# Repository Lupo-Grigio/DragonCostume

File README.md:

# DragonCostume 
Repository for all code and designs used in my massive dragon head and costume

/Dragon Head 

  -/Lights 
    Internal LED strips
    Running WLED on an esp32 to power the primary LED Light Strips within the head (Fork minimal changes) (Dev environment is Platform.io in VSCode)
    The strip "Map" or definitions are created from a google sheets spreadsheet, The regions are created using several pivot tables

    -/WLED
      clone of WLED source from https://github.com/Aircoookie/WLED I _think_ this directory should be a fork.. but maybe if I actually make changes. this tweak is to get WLED to work on one of @romkey's discoball ESP32-dev boards. 

    -/WoWki Simulations
      Several test FASTLED simulations of the head strips coded up in WoKwi - no production code
      makes a convient(Where is my spell checker?) way to simulate the LED strips.

  -/Eyes Controllable Animated Eyes
    Animated Eyes powered by an Adafruit Monster M4sk with custom code (fork) (Dev environment is both Arduino and Platform.io)
    Animated eye gaze direction is controlled by face detection done on an ESP32-WROVER-DEV Test framework is based on the ESP32-cam "camera" demo(Dev environment is both Arduino and Platform.io, but issue with Platform.io causes mem management failure in face detection)
    Some example code created for sscanf and parameter passing coded in wowki
    Physical Joystic control of the eyes powered by an ADAFRUIT Joy Feather and Feather wing : In Progress

      -/M4_Eyes Based off of TonyLHansen's merge request into Adafruit's main. His code includes some extra eye controls and code for user.cpp files getting config info from the config file. Will be handy for me to set the BAUD rate between controller and the mask. https://github.com/adafruit/Adafruit_Learning_System_Guides/pull/915/commits/2b4827c8276a8fa8b2f16dbccf2c00a39fa4a631
    
      -/ESP32-Eye-Tracker
        Based on the ESP32-Camera-Eye-tracker-DEMO, Wifi removed, with web server assocated code removed. This Just captures video and does face detection, if it finds a face it writes it out to serial2
        Face detection running in the DEMO gets about 2.3 frames a second
        Face detection running in the Eye Tracker about 2.7 This ended up being a bit of a waste of time. I strongly suspect the face recognition is baced on OpenCV's v3 HAAR cascade face detection rather than the better, smaller, more efficient DNN face detection which appeared in opencv 4 (or 4.1 can't remember to lazy to look up). 

      -/ESP32-Camera-Eye-tracker-DEMO
      Cloned from the ESP32-CAM/example and fixed via this commentary https://github.com/espressif/arduino-esp32/issues/5128. This directory contains the mirror code for M4_Eyes, this is the "controller" part. This does facial detection, and sends tracking data out serial port. This code is written for the Freenove ESP32-WROVER-DEV module with camera. https://www.amazon.com/Freenove-ESP32-WROVER-Bluetooth-Compatible-Tutorials/dp/B09BC5CNHM?ref_=ast_sto_dp This demo code runs a webserver and streams video, and contains VERBOSE debugging info written to the USB serial port. Face location data is written to serial 2 which is configured on pins 2 and 15, the format of the message and which pin is TX and RX are in the code. 

      -/Prototype Case
      3d printable case for the face tracking eye demo. Designed to hold the ESP32-CAM module and the Adafruit Monster M4sk. Originally designed in tinkercad by importing the case designed by adafruit for the M4sk. Tinkercad link:https://www.tinkercad.com/things/l33OCsHAKPb-eye-camera-mask-case also can be found on thingaverse: https://www.thingiverse.com/thing:5188566

      -/M4SK PWM remapping example
      Sample code for the Adafruit M4SK that just remaps the PWM port as Serial2 reads from it and writes to the USB serial monitor

      -/ESP32-CAM second serial sample
      A tiny project containing an example of setting up an ESP32-CAM to write data to pins 15 and 2, also a bit of beginner examples of passing pointers and structs. Developed and simulated on Wokwi. See the Wokwi-project.txt for link

  -Forward Cameras and Performer HUD
    External visability to performer provided by external cameras powered by ESP32-CAM modules sending their display info to : In Progress
    Heds Up Display Rig has yet to be speced and designed
    
  -Voice Commands
    Voice commands provided by dedicated arduino compatable voice command recognizer TBD
  
  -Voice Tweaker
    Standard voice changer running on an Arduino nano sense 33 (because I've got 2 of them and they have built in microphones)
    
  -Smoke System
    Smoke effect controlled by arduino TBD

  -/Physical 
    Sculpture and internal structure
    The Head itself is 3d modeled in blender
    The shell of the Mask is created thorugh pepacura designer https://tamasoft.co.jp/pepakura-en/
    The shell is cut both on a Silhouette Cameo 4 and a generic 60watt RUIDA powered Co2 laser
    Internal LED supports designed in Fusion 360 AND Tinkercad
    Animated Eye Mounts designed in Fusion 360 and Tinkercad
    All printed using PRUSASLICER

    -/Blender Models
      this is the start of the workflow, Just as it says, the blender source for the shell.
    
    -/Pepakura
      source files for the Shell generated using pepakura designer https://tamasoft.co.jp/pepakura-en/

    -/Laser
      RLD and DXF files for the shell cut paths

    -Internal LED supports
    The 3dprinted internal struts for the LEDs where designed in Fusion 360, then modified in tinkercad to ad direction registration and numbering then pulled into PrusaSlicer to prep for 3d printing. 

  -Cosmetic wrapping
    Reflective pattern created in Shilouette studio and cut on a Shilouette CAMEO 4
    
Top Hat
    LED strip and ElWire controlled by TBD (Likely an ESP32 running WLED to synch with the dragon head
    Reflective pattern created in Shilouette studio and cut on a Shilouette CAMEO 4
    
Swagger Stick
    Bulb Internal LEDs controlled by TBD (likely an ESP32 runing WLED to synch with the dragon head
    physical controls on the stick and white LEDs in the base, as well as discoball magnetic attachment to base. 
    
Jacket
    Reflective pattern created in Shilouette studio and cut on a Shilouette CAMEO 4
    "Scales" and supports for the reflective patterns designed in Fusion360 and tinkercad
    "Scales" and supports Sliced and printed using PrusaSlicer
    Jacket Internal lights powered by an ESP32 running WLED
    
Vest
    Vest pattern created in Shilouette studio and cut on a Shilouette CAMEO 4
    "Scales" and supports for the reflective patterns designed in Fusion360 and tinkercad
    "Scales" and supports Sliced and printed using PrusaSlicer
    
Broken Heart
    broken heart pattern created in Shilouette studio and cut on a Shilouette CAMEO 4
    Internal lighting controlled by an arduino nano running simple FASTLED animations
    
Pants
    Pants pattern created in Shilouette studio and cut on a Shilouette CAMEO 4
    "Scales" and supports for the reflective patterns designed in Fusion360 and tinkercad
    "Scales" and supports Sliced and printed using PrusaSlicer

Gloves
    Glove pattern created in Shilouette studio and cut on a Shilouette CAMEO 4
    "Scales" and supports for the reflective patterns designed in Fusion360 and tinkercad
    "Scales" and supports Sliced and printed using PrusaSlicer
    Button controls integrated into the gloves managed by an arduino nano and sent to various devices

Shoes
    Vest pattern created in Shilouette studio and cut on a Shilouette CAMEO 4
    "Scales" and supports for the reflective patterns designed in Fusion360 and tinkercad
    "Scales" and supports Sliced and printed using PrusaSlicer

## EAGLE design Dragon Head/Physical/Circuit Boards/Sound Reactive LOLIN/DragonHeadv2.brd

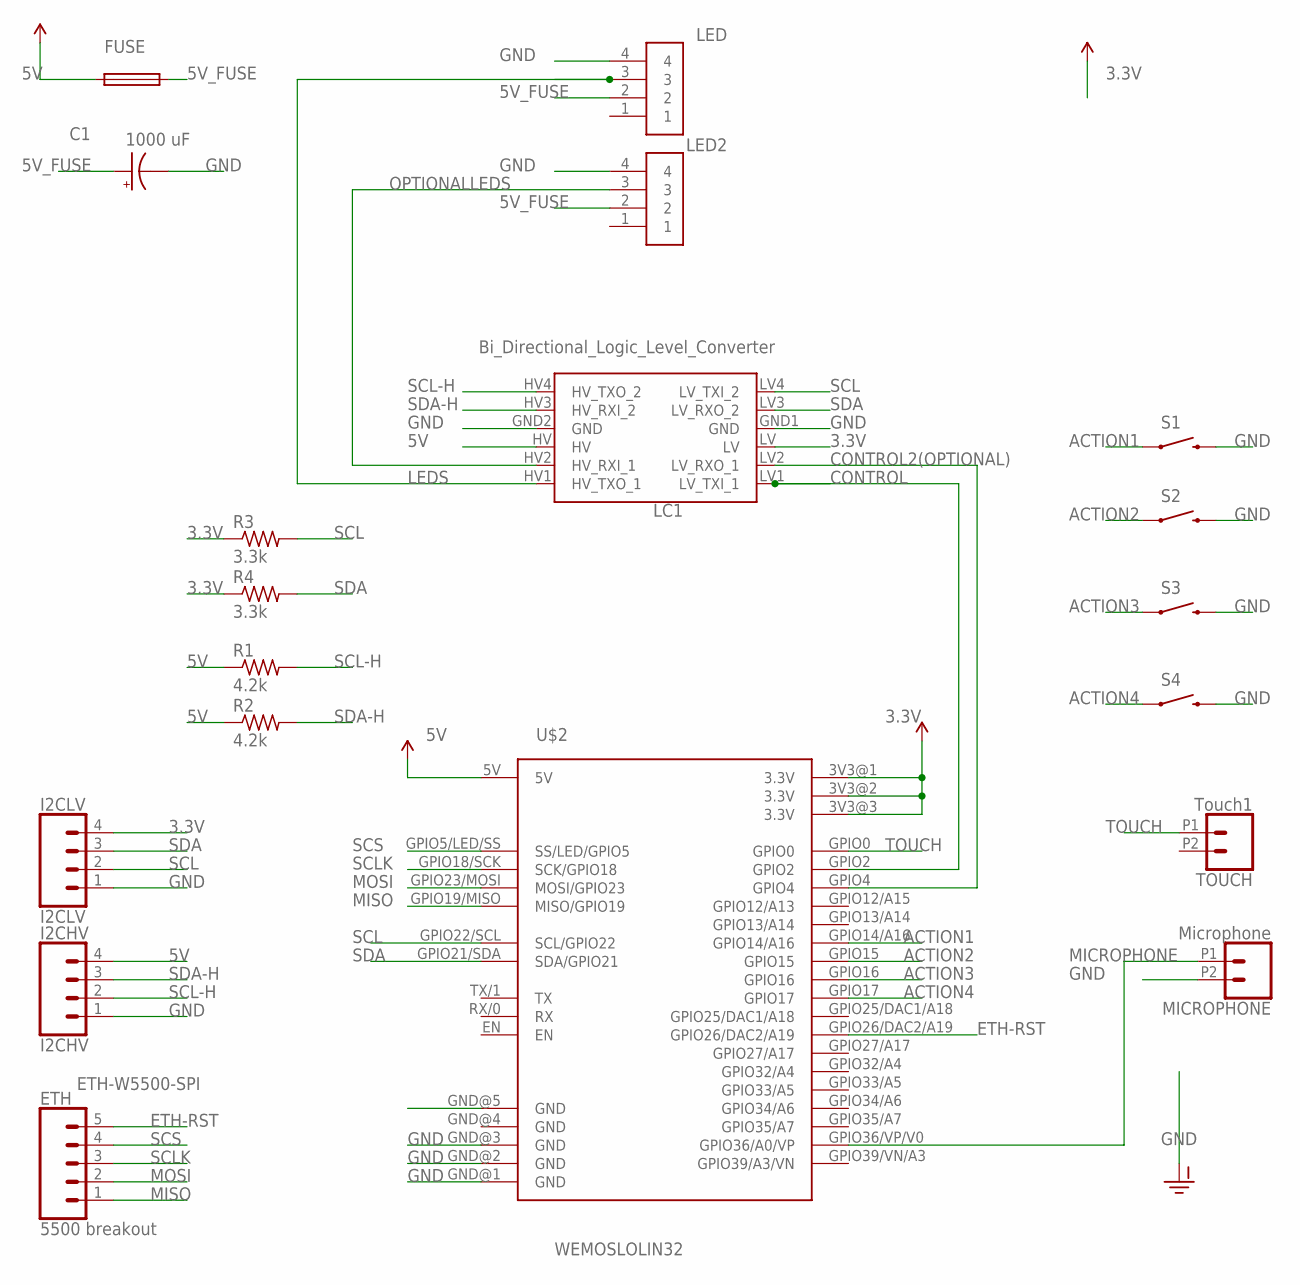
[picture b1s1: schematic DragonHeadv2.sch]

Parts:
C1: 1000 uF; CPOL-RADIAL-5MM-10MM
ETH: 5500 breakout; 1X05
FUSE: FUSEBLANK_5X20MM; FUSE_HOLDER_5X20MM
I2CHV: I2CHV; 1X04
I2CLV: I2CLV; 1X04
LC1: Bi_Directional_Logic_Level_Converter; SPARKFUN_LOGIC_LEVEL_CONVERTER
LED, LED2: 231-334/001-000; WAGO_231-334/001-000
MICROPHONE: Microphone; 1X02_2.54_SCREWTERM
R1, R2: 4.2k; 0204/7
R3, R4: 3.3k; 0204/7
S1, S2, S3, S4: SWITCH-MOMENTARY-2SIDE_EZ; TACTILE-PTH-SIDEEZ
TOUCH: Touch1; 1X02_2.54_SCREWTERM
U$2: WEMOSLOLIN32; LOLIN32VAR1

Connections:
3.3V: I2CLV.4, LC1.LV, R3.1, R4.1, U$2.3V3@1 (3.3V), U$2.3V3@2 (3.3V), U$2.3V3@3 (3.3V)
5V: FUSE.2, I2CHV.4, LC1.HV, R1.1, R2.1, U$2.5V
5V_FUSE: C1.+, FUSE.1, LED.2, LED2.2
ACTION1: S1.1, U$2.GPIO14/A16
ACTION2: S2.1, U$2.GPIO15
ACTION3: S3.1, U$2.GPIO16
ACTION4: S4.1, U$2.GPIO17
CONTROL: LC1.LV1 (LV_TXI_1), U$2.GPIO2
CONTROL2(OPTIONAL): LC1.LV2 (LV_RXO_1), U$2.GPIO4
ETH-RST: ETH.5, U$2.GPIO26/DAC2/A19
GND: C1.-, I2CHV.1, I2CLV.1, LC1.GND1 (GND), LC1.GND2 (GND), LED.4, LED2.4, MICROPHONE.P2 (2), S1.2, S2.2, S3.2, S4.2, U$2.GND@1 (GND), U$2.GND@2 (GND), U$2.GND@3 (GND), U$2.GND@5 (GND)
LEDS: LC1.HV1 (HV_TXO_1), LED.3
MICROPHONE: MICROPHONE.P1 (1), U$2.GPIO36/VP/V0 (GPIO36/A0/VP)
MISO: ETH.1, U$2.GPIO19/MISO (MISO/GPIO19)
MOSI: ETH.2, U$2.GPIO23/MOSI (MOSI/GPIO23)
OPTIONALLEDS: LC1.HV2 (HV_RXI_1), LED2.3
SCL: I2CLV.2, LC1.LV4 (LV_TXI_2), R3.2, U$2.GPIO22/SCL (SCL/GPIO22)
SCL-H: I2CHV.2, LC1.HV4 (HV_TXO_2), R1.2
SCLK: ETH.3, U$2.GPIO18/SCK (SCK/GPIO18)
SCS: ETH.4, U$2.GPIO5/LED/SS (SS/LED/GPIO5)
SDA: I2CLV.3, LC1.LV3 (LV_RXO_2), R4.2, U$2.GPIO21/SDA (SDA/GPIO21)
SDA-H: I2CHV.3, LC1.HV3 (HV_RXI_2), R2.2
TOUCH: TOUCH.P1 (1), U$2.GPIO0

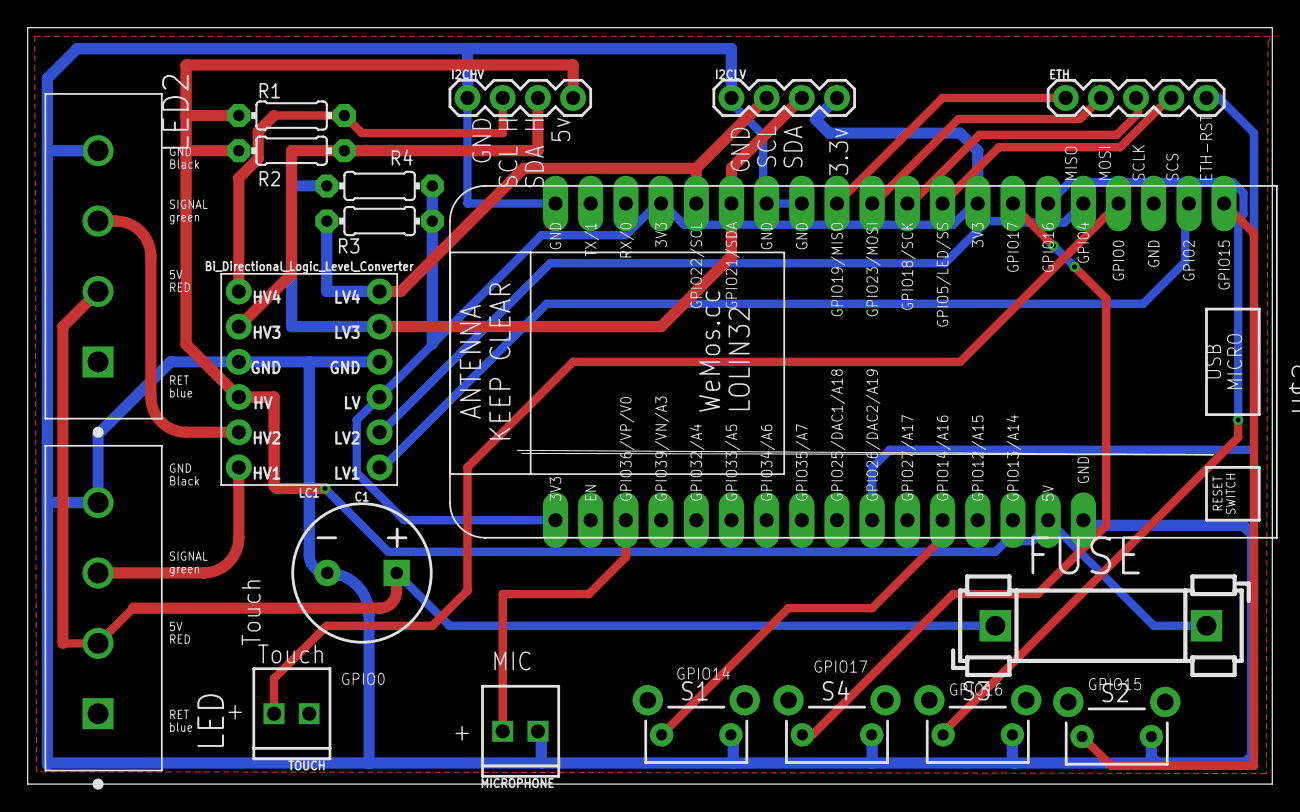
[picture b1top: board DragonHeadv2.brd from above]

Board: 2 copper layers, 89.8 x 54.6 mm, 19 parts (0 on the bottom side), 23 nets.

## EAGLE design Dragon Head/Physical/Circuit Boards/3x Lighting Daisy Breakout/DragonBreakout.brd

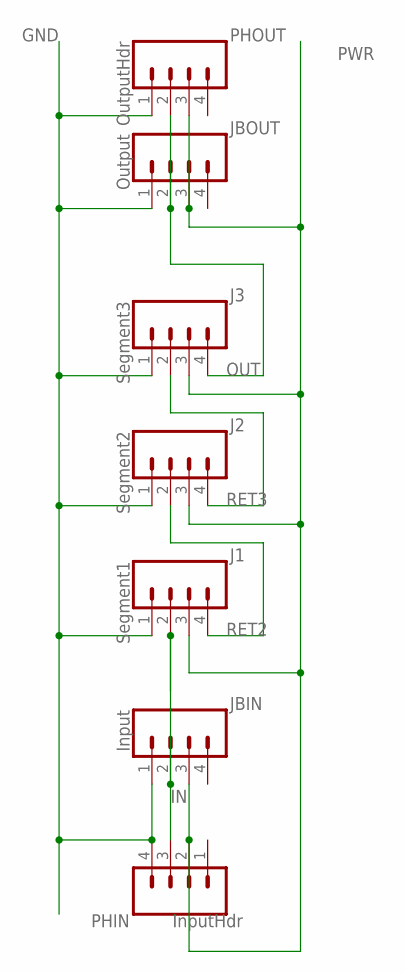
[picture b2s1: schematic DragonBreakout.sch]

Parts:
J1: Segment1; SCREWTERMINAL-3.5MM-4_LOCK
J2: Segment2; SCREWTERMINAL-3.5MM-4_LOCK
J3: Segment3; SCREWTERMINAL-3.5MM-4_LOCK
JBIN: Input; SCREWTERMINAL-3.5MM-4_LOCK
JBOUT: Output; SCREWTERMINAL-3.5MM-4_LOCK
PHIN: InputHdr; 1X04
PHOUT: OutputHdr; 1X04

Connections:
GND: J1.1, J2.1, J3.1, JBIN.1, JBOUT.1, PHIN.4, PHOUT.1
IN: J1.2, JBIN.2, PHIN.3
OUT: J3.4, JBOUT.2, PHOUT.2
PWR: J1.3, J2.3, J3.3, JBIN.3, JBOUT.3, PHIN.2, PHOUT.3
RET2: J1.4, J2.2
RET3: J2.4, J3.2

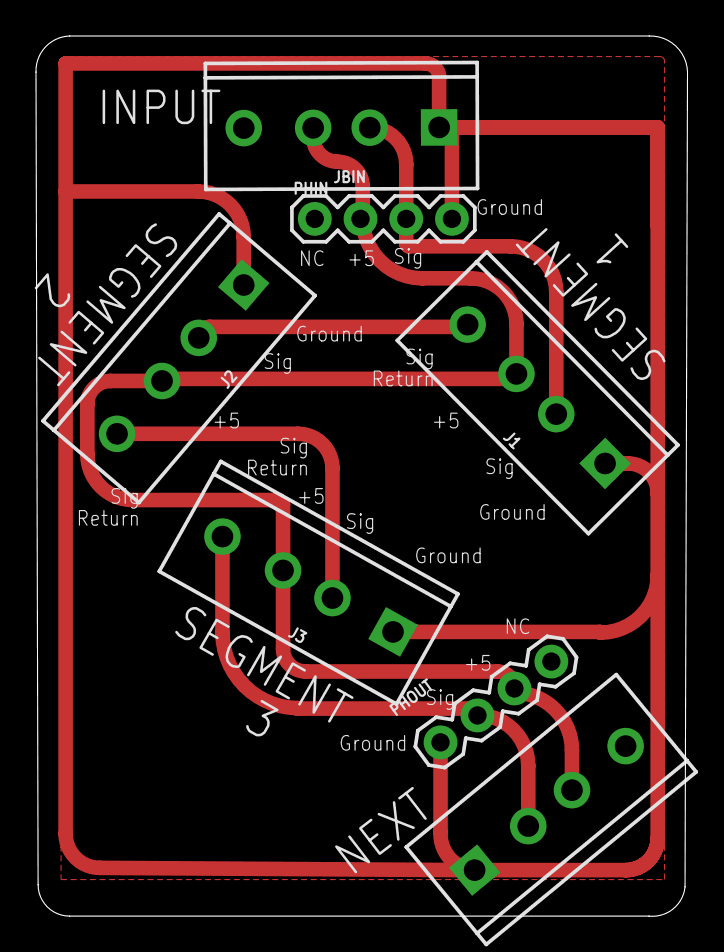
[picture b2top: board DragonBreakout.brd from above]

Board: 2 copper layers, 36.2 x 48.9 mm, 7 parts (0 on the bottom side), 6 nets.

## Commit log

2022-01-04 Original Creation of Readme
    Project structure outline
2022-01-05 Getpod initialized
2022-01-05 Cloned from TonyLHansen commit to Monster M4sk
2022-01-06 creation of ESP32_Camera_Controller_Demo
2022-01-06 Prototype Case
2022-01-06 Initial commit of dragon head physical 3d model and wokwi light strip simulations
2022-01-06 Adding 3d models, pepakura source and laser cut files for the shell
2022-01-06 Added before image for the interal supports
2022-01-06 minor update to Readme.md
2022-01-06 Re-arrangement of user.cpp fixing up globals.h
2022-01-06 had to comment out user_setup(doc); in file.cpp but this works, eyes track faces
2022-01-06 Renamed the ESP32 camera code to something les dystopian
2022-01-06 WLED version running dragon head
2022-01-06 documentation update
2022-01-06 Optimized Face Finder compiles....
2022-01-06 Increased Baud removed serial blocks on startup
2022-01-06 minor update on readme
2022-01-07 Refactoring, renaming for clarity, Variable Rang
2022-01-07 Ifdefed verbose debug fixed Y val bug
2022-01-07 added wowki scrap for testing parameters and sprin
2022-01-08 Implemented dynamic scaling and fixed minor bug
2022-01-08 Oooh it works SO WELL!!!
2022-01-08 Changes to fix range issues. X and Y now work
2022-01-08 Fixing bugs and using the same code as the Face-Finder
2022-01-08 Demo Works... with the eyes, kinda... something about it crashes the eyes. maybe in demo mode 155200 is to fast?
2022-01-22 Just finished base model for V2.1
2022-01-22 added vs code workspace
2022-01-22 minor tweak before going to Pepakura
2022-01-22 Pepacura finished v2.1 savedd as svg and dxf per page
2022-01-22 tidying up pepakura files
2022-02-11 Updated head 2.1 with pepakura and silhouette stud
2022-02-12 WLED update
2022-02-15 Silhouette pass complete v 2.1 svg version export
2022-02-17 layout updates
2022-03-29 Working on I2C comms between 2 masks
2022-03-29 Mask Design v2.1 files plus 2 pair eyes synch over i2c
2022-04-01 WLED directory update
2022-04-04 I2C Library works
2022-04-07 Why is gaze library not in my git hub
2022-04-07 commiting to make sure my gaze library v1.0 is on git hub
2022-04-09 M4_Eyes I2C stubbed in I2C test works.
2022-04-09 M4sk sketch to test I2C without eye code
2022-04-10 DUAL EYE CONTROL WORKS
2022-04-10 DUAL M4SK tracking works!
2022-04-15 Adding Tympanic Case V1.0
2022-04-15 Adding Assembly Guide pictures
2022-04-15 tympanic case assembly instructions
2022-04-15 Assembly instructions
    Added Assembly Instructions in README.md
2022-04-15 Readme Edit
2022-04-15 fixed .
2022-04-16 Adding first version of Circuit board case
2022-04-21 Circuit Boards
2022-05-02 Cases Checking
2022-05-11 Dragon Vision Camera and web server Initial version

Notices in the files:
parts and their libraries:
SparkFun-Connectors: Licensing: Creative Commons ShareAlike 4.0 International - https://creativecommons.org/licenses/by-sa/4.0
SparkFun-Electromechanical: Licensing: CC v3.0 Share-Alike You are welcome to use this library for commercial purposes.
